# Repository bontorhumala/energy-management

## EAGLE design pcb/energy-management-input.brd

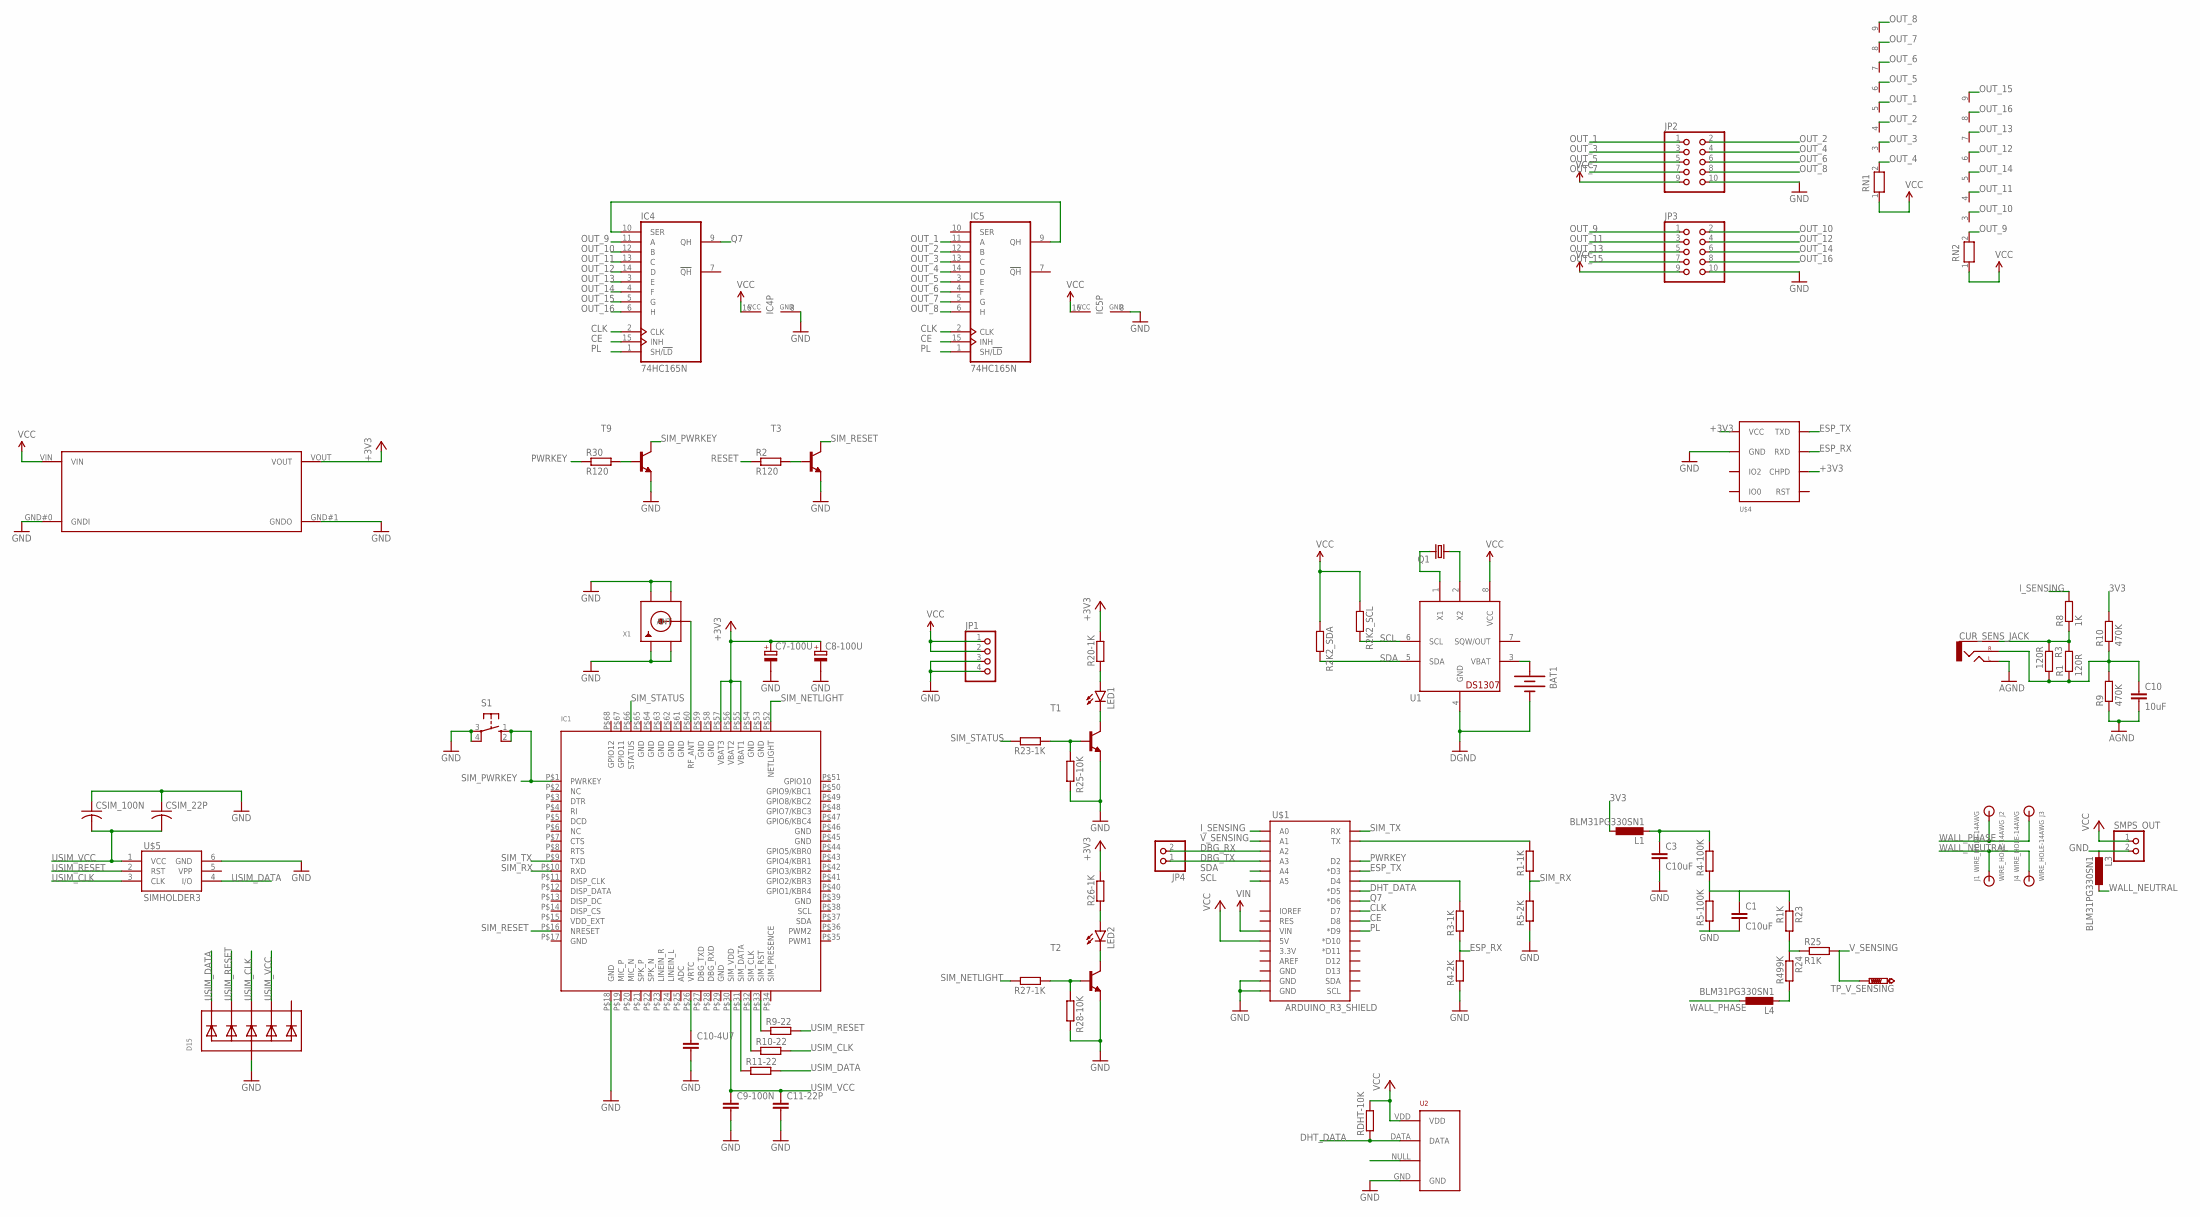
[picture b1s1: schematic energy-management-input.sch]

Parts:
BAT1: BATTERY20PTH; BATTCOM_20MM_PTH
C1, C3: C10uF; C0805
C7-100U, C8-100U: CPOL-EU153CLV-0605; 153CLV-0605
C9-100N, C10-4U7, C11-22P: C-EUC0603; C0603
C10: 10uF; C0805
CSIM_22P, CSIM_100N: C-USC0603K; C0603K
CUR_SENS_JACK: AUDIO-JACKSMD2; AUDIO-JACK-3.5MM-SMD
D15: TVSARRAY_5LANE; SOT363
IC1: GSM_SIM900_LITERAL; SIM900_SMT
IC4, IC5: 74HC165N; DIL16
J1, J2, J3, J4: WIRE_HOLE-14AWG
JP1: PINHD-1X4; 1X04
JP2, JP3: PINHD-2X5; 2X05
JP4: PINHD-1X2; 1X02
L1, L3, L4: BLM31PG330SN1; L3216C
LED1, LED2: LED-3MM-NO_SILK; LED3MM-NS
Q1: CRYSTALTC26H; TC26H
R1: 120R; 0204/7
R1-1K, R2K2_SCL, R2K2_SDA, R3-1K, R4-2K, R5-2K, R9-22, R10-22, R11-22, R20-1K, R23-1K, R25-10K, R26-1K, R27-1K, R28-10K: R-EU_R0603; R0603
R2, R30: R120; M0805
R3: 120R; R1206
R4-100K, R5-100K: R-EU_R0805; R0805
R8: 1K; R0805
R9, R10: 470K; R0805
R23, R25: R1K; R0805
R24: R499K; R0805
RDHT-10K: R-EU_R0603; R0603
RN1, RN2: RN08; RN-9
S1: 10-XX; B3F-10XX
SMPS_OUT: PINHD-1X2; 1X02
T1, T2, T3, T9: MMBT2222ALT1-NPN-SOT23-BEC; SOT23-BEC
TP_V_SENSING: PTR1PAD1-13; P1-13
U1: DS1307; DIL08
U2: RHT03_DHT-22_AM2302; RHT03_DHT-22
U$1: ARDUINO_R3_SHIELD; UNO_R3_SHIELD
U$2: DCDCMODULE
U$4: ESP8266
U$5: SIMHOLDER3
X1: SMACONNECTOR; SMA90_DIP

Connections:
3V3: L1.1, R10.2
+3V3: C7-100U.+, C8-100U.+, IC1.P$55 (VBAT1), IC1.P$56 (VBAT2), IC1.P$57 (VBAT3), R20-1K.2, R26-1K.2, U$2.VOUT, U$4.CHPD, U$4.VCC
AGND: C10.2, CUR_SENS_JACK.TIP (LEFT), R9.1
CE: IC4.15 (INH), IC5.15 (INH), U$1.D8
CLK: IC4.2 (CLK), IC5.2 (CLK), U$1.D7
DBG_RX: JP4.2, U$1.A2
DBG_TX: JP4.1, U$1.A3
DHT_DATA: RDHT-10K.1, U2.DATA, U$1.D5 (*D5)
ESP_RX: R3-1K.1, R4-2K.2, U$4.RXD
ESP_TX: U$1.D3 (*D3), U$4.TXD
GND: BAT1.2 (-), C1.2, C3.2, C7-100U.-, C8-100U.-, C9-100N.2, C10-4U7.2, C11-22P.2, CSIM_22P.1, CSIM_100N.1, D15.2 (A), IC1.P$17 (GND), IC1.P$18 (GND), IC1.P$29 (GND), IC1.P$39 (GND), IC1.P$45 (GND), IC1.P$46 (GND), IC1.P$53 (GND), IC1.P$54 (GND), IC1.P$58 (GND), IC1.P$59 (GND), IC1.P$61 (GND), IC1.P$62 (GND), IC1.P$63 (GND), IC1.P$64 (GND), IC1.P$65 (GND), IC4.8 (GND), IC5.8 (GND), JP1.3, JP1.4, JP2.10, JP3.10, L3.2, R4-2K.1, R5-2K.1, R5-100K.1, R25-10K.2, R28-10K.2, S1.3, S1.4 (P1), SMPS_OUT.2, T1.E, T2.E, T3.E, T9.E, U1.4 (GND), U2.GND, U$1.GND@0 (GND), U$1.GND@1 (GND), U$2.GND#0 (GNDI), U$2.GND#1 (GNDO), U$4.GND, U$5.6 (GND), X1.GND1, X1.GND2, X1.GND3, X1.GND4
GPIO11: IC1.P$67 (GPIO11)
GPIO12: IC1.P$68 (GPIO12)
I_SENSING: R8.2, U$1.A0
unnamed: C3.1, L1.2, R4-100K.2
unnamed: IC1.P$31 (SIM_DATA), R11-22.1
unnamed: IC1.P$32 (SIM_CLK), R10-22.1
unnamed: IC1.P$33 (SIM_RST), R9-22.1
unnamed: C10-4U7.1, IC1.P$26 (VRTC)
unnamed: IC1.P$60 (RF_ANT), X1.ANTENNA (ANT)
unnamed: R1-1K.2, U$1.TX
unnamed: LED1.A, R20-1K.1
unnamed: LED1.K (C), T1.C
unnamed: R23-1K.1, R25-10K.1, T1.B
unnamed: LED2.A, R26-1K.1
unnamed: LED2.K (C), T2.C
unnamed: R27-1K.1, R28-10K.1, T2.B
unnamed: R30.2, T9.B
unnamed: R2.2, T3.B
unnamed: Q1.1, U1.2 (X2)
unnamed: R3-1K.2, U$1.D4
unnamed: Q1.2, U1.1 (X1)
unnamed: C1.1, R4-100K.1, R5-100K.2, R23.1
unnamed: R23.2, R24.1, R25.1
unnamed: L4.2, R24.2
unnamed: BAT1.1 (+), U1.3 (VBAT)
unnamed: CUR_SENS_JACK.SLEEVE, R1.2, R3.1, R8.1
unnamed: C10.1, CUR_SENS_JACK.RING (RIGHT), R1.1, R3.2, R9.2, R10.1
unnamed: IC4.10 (SER), IC5.9 (QH)
OUT_1: IC5.11 (A), JP2.1, RN1.5
OUT_2: IC5.12 (B), JP2.2, RN1.4
OUT_3: IC5.13 (C), JP2.3, RN1.3
OUT_4: IC5.14 (D), JP2.4, RN1.2
OUT_5: IC5.3 (E), JP2.5, RN1.6
OUT_6: IC5.4 (F), JP2.6, RN1.7
OUT_7: IC5.5 (G), JP2.7, RN1.8
OUT_8: IC5.6 (H), JP2.8, RN1.9
OUT_9: IC4.11 (A), JP3.1, RN2.2
OUT_10: IC4.12 (B), JP3.2, RN2.3
OUT_11: IC4.13 (C), JP3.3, RN2.4
OUT_12: IC4.14 (D), JP3.4, RN2.6
OUT_13: IC4.3 (E), JP3.5, RN2.7
OUT_14: IC4.4 (F), JP3.6, RN2.5
OUT_15: IC4.5 (G), JP3.7, RN2.9
OUT_16: IC4.6 (H), JP3.8, RN2.8
PL: IC4.1 (SH/!LD), IC5.1 (SH/!LD), U$1.D9 (*D9)
PWRKEY: R30.1, U$1.D2
Q7: IC4.9 (QH), U$1.D6 (*D6)
RESET: R2.1
SCL: R2K2_SCL.2, U1.6 (SCL), U$1.A5
SDA: R2K2_SDA.2, U1.5 (SDA), U$1.A4
SIM_NETLIGHT: IC1.P$52 (NETLIGHT), R27-1K.2
SIM_PWRKEY: IC1.P$1 (PWRKEY), S1.1 (S), S1.2 (S1), T9.C
SIM_RESET: IC1.P$16 (NRESET), T3.C
SIM_RX: IC1.P$10 (RXD), R1-1K.1, R5-2K.2
SIM_STATUS: IC1.P$66 (STATUS), R23-1K.2
SIM_TX: IC1.P$9 (TXD), U$1.RX
USIM_CLK: D15.4 (C3), R10-22.2, U$5.3 (CLK)
USIM_DATA: D15.1 (C1), R11-22.2, U$5.4 (I/O)
USIM_RESET: D15.3 (C2), R9-22.2, U$5.2 (RST)
USIM_VCC: C9-100N.1, C11-22P.1, CSIM_22P.2, CSIM_100N.2, D15.5 (C4), IC1.P$30 (SIM_VDD), U$5.1 (VCC)
VCC: IC4.16 (VCC), IC5.16 (VCC), JP1.1, JP1.2, JP2.9, JP3.9, R2K2_SCL.1, R2K2_SDA.1, RDHT-10K.2, RN1.1, RN2.1, SMPS_OUT.1, U1.8 (VCC), U2.VDD, U$1.5V, U$2.VIN
VIN: U$1.VIN
V_SENSING: R25.2, TP_V_SENSING.TP, U$1.A1
WALL_NEUTRAL: J1.P$1, J4.P$1, L3.1
WALL_PHASE: J2.P$1, J3.P$1, L4.1

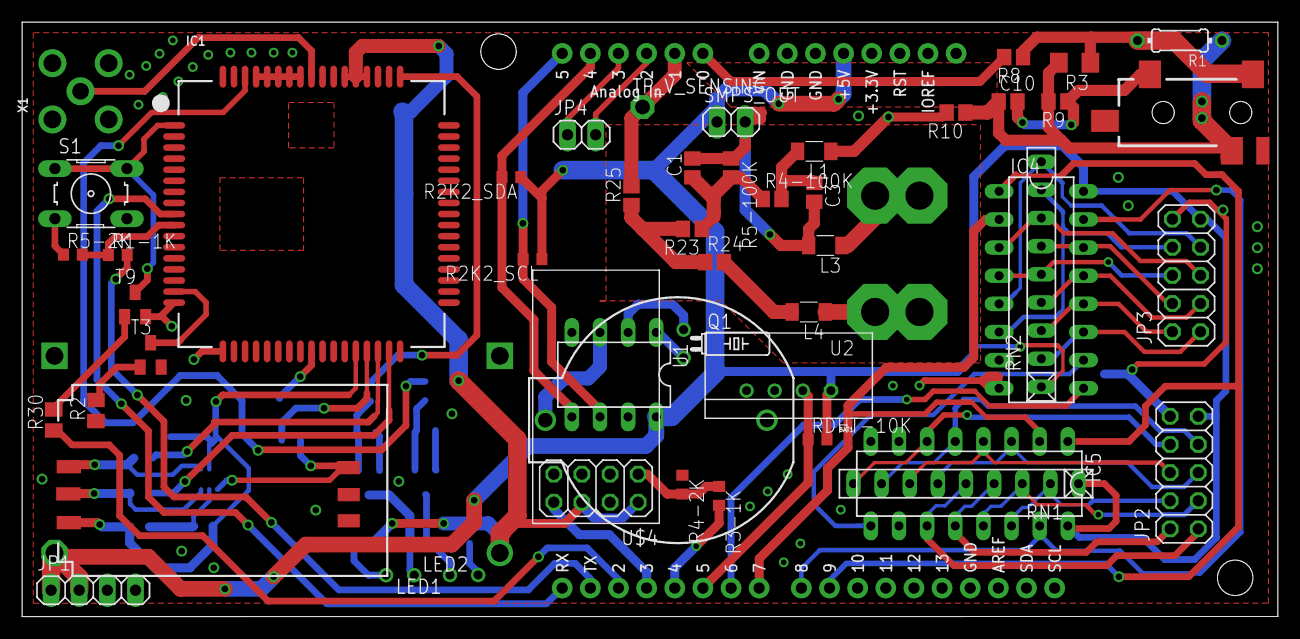
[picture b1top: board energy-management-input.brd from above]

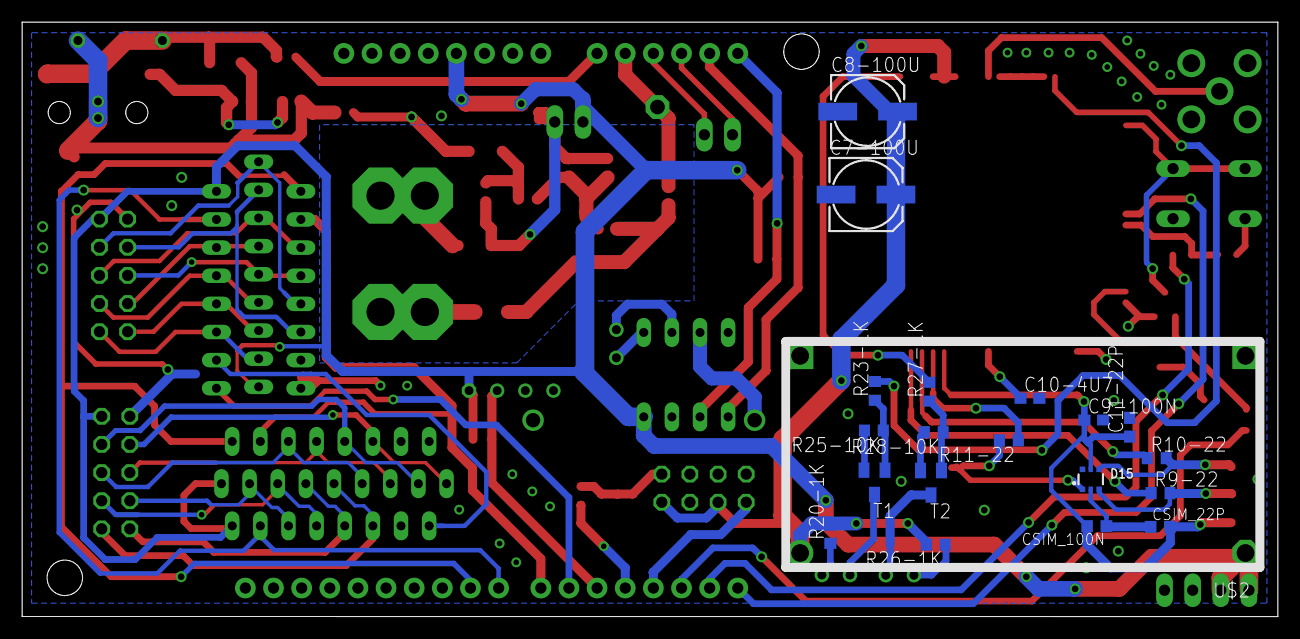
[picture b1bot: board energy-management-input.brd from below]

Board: 2 copper layers, 113.3 x 53.7 mm, 74 parts (20 on the bottom side), 72 nets.

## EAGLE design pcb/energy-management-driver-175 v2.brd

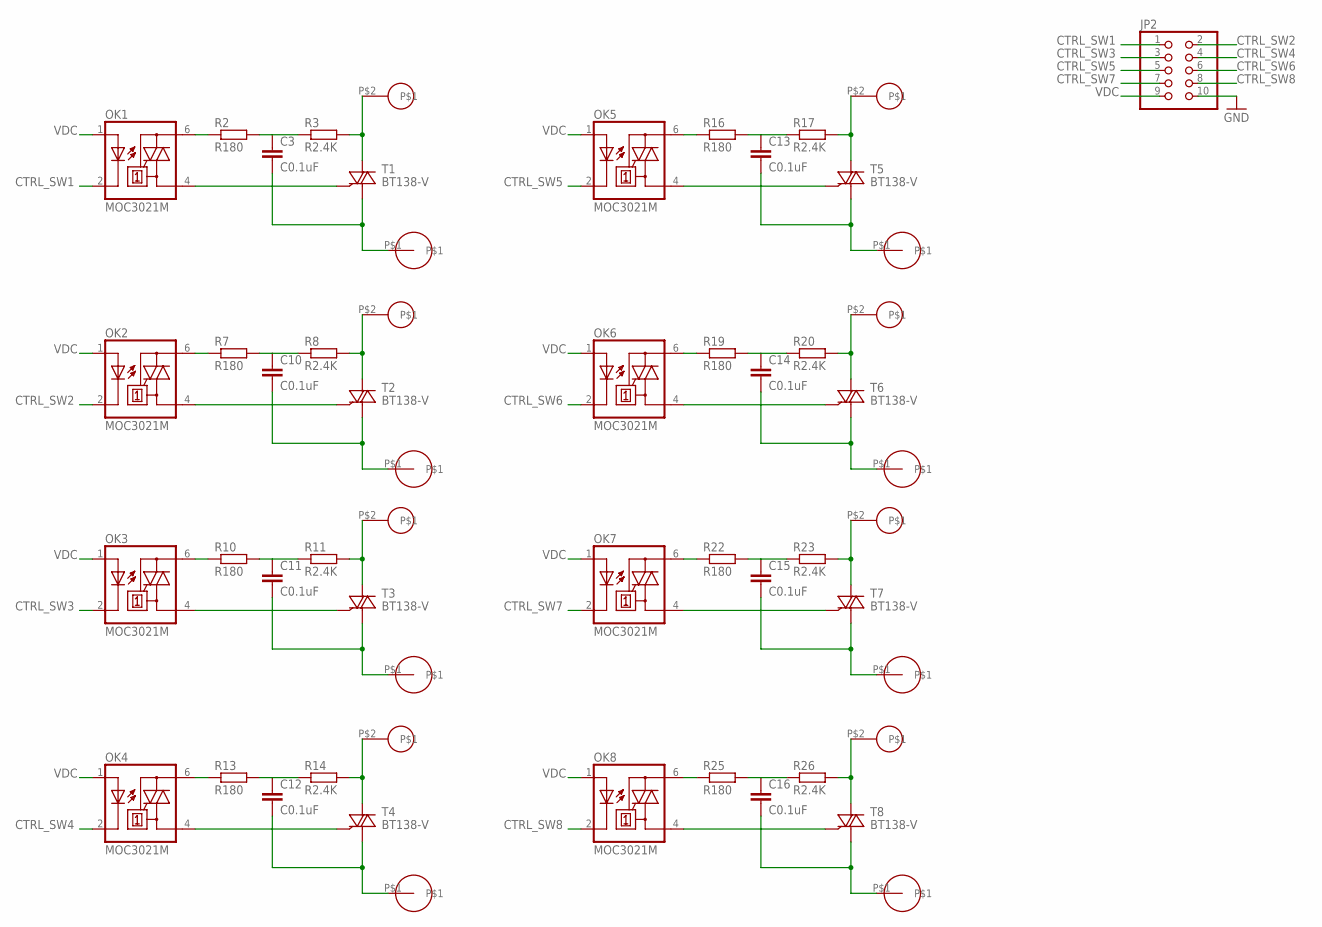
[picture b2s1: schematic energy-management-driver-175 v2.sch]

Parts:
C3, C10, C11, C12, C13, C14, C15, C16: C0.1uF; C0805
JP2: PINHD-2X5; 2X05
OK1, OK2, OK3, OK4, OK5, OK6, OK7, OK8: MOC3021M; DIL06
R2, R7, R10, R13, R16, R19, R22, R25: R180; M0805
R3, R8, R11, R14, R17, R20, R23, R26: R2.4K; M0805
T1, T2, T3, T4, T5, T6, T7, T8: BT138-V; TO220BV
U$1, U$2, U$3, U$4, U$5, U$6, U$7, U$8: CONN-SKUN
U$9, U$10, U$11, U$12, U$13, U$14, U$15, U$16: CONN-CABLE

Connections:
CTRL_SW1: JP2.1, OK1.2 (C)
CTRL_SW2: JP2.2, OK2.2 (C)
CTRL_SW3: JP2.3, OK3.2 (C)
CTRL_SW4: JP2.4, OK4.2 (C)
CTRL_SW5: JP2.5, OK5.2 (C)
CTRL_SW6: JP2.6, OK6.2 (C)
CTRL_SW7: JP2.7, OK7.2 (C)
CTRL_SW8: JP2.8, OK8.2 (C)
GND: JP2.10
unnamed: OK1.6 (A2), R2.1
unnamed: C3.1, R2.2, R3.1
unnamed: OK1.4 (A1), T1.G
unnamed: C3.2, T1.T1 (A1), U$9.P$1
unnamed: R3.2, T1.T2 (A2), U$1.P$2
unnamed: OK2.6 (A2), R7.1
unnamed: C10.1, R7.2, R8.1
unnamed: OK2.4 (A1), T2.G
unnamed: C10.2, T2.T1 (A1), U$11.P$1
unnamed: OK3.6 (A2), R10.1
unnamed: C11.1, R10.2, R11.1
unnamed: OK3.4 (A1), T3.G
unnamed: C11.2, T3.T1 (A1), U$14.P$1
unnamed: OK4.6 (A2), R13.1
unnamed: C12.1, R13.2, R14.1
unnamed: OK4.4 (A1), T4.G
unnamed: C12.2, T4.T1 (A1), U$13.P$1
unnamed: OK5.6 (A2), R16.1
unnamed: C13.1, R16.2, R17.1
unnamed: OK5.4 (A1), T5.G
unnamed: C13.2, T5.T1 (A1), U$10.P$1
unnamed: OK6.6 (A2), R19.1
unnamed: C14.1, R19.2, R20.1
unnamed: OK6.4 (A1), T6.G
unnamed: C14.2, T6.T1 (A1), U$12.P$1
unnamed: OK7.6 (A2), R22.1
unnamed: C15.1, R22.2, R23.1
unnamed: OK7.4 (A1), T7.G
unnamed: C15.2, T7.T1 (A1), U$15.P$1
unnamed: OK8.6 (A2), R25.1
unnamed: C16.1, R25.2, R26.1
unnamed: OK8.4 (A1), T8.G
unnamed: C16.2, T8.T1 (A1), U$16.P$1
unnamed: R8.2, T2.T2 (A2), U$2.P$2
unnamed: R11.2, T3.T2 (A2), U$3.P$2
unnamed: R14.2, T4.T2 (A2), U$4.P$2
unnamed: R26.2, T8.T2 (A2), U$5.P$2
unnamed: R23.2, T7.T2 (A2), U$6.P$2
unnamed: R20.2, T6.T2 (A2), U$7.P$2
unnamed: R17.2, T5.T2 (A2), U$8.P$2
VDC: JP2.9, OK1.1 (A), OK2.1 (A), OK3.1 (A), OK4.1 (A), OK5.1 (A), OK6.1 (A), OK7.1 (A), OK8.1 (A)

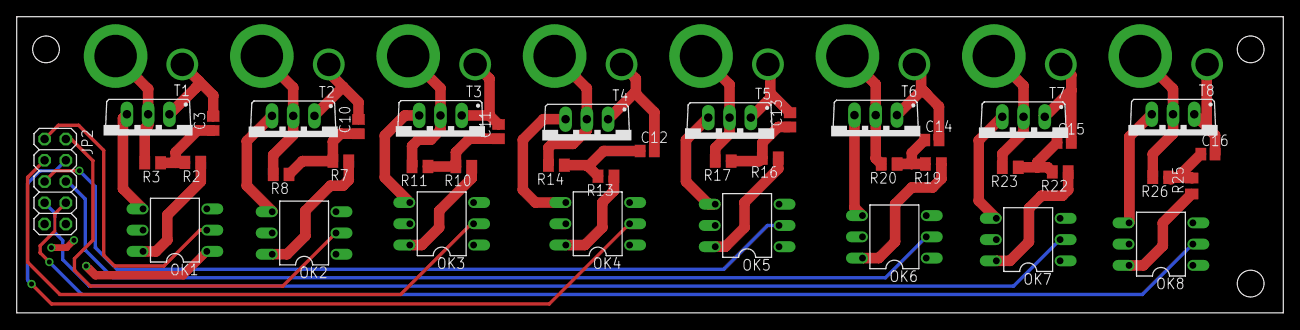
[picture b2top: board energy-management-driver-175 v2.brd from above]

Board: 2 copper layers, 151.4 x 35.4 mm, 57 parts (0 on the bottom side), 49 nets.

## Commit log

2014-12-03 :confetti_ball: Added .gitattributes & .gitignore files
2014-12-03 initial addition: pcb and sketch
2014-12-03 added voltage and current measurement circuit
2014-12-03 routing shift register
2014-12-04 pcb with shift register and dht22
2014-12-04 put batt and reg on bottom, dht, ds, wifi on top
2014-12-04 remove resistor and cutout on analog line
2014-12-04 add hole
2014-12-04 move via
2014-12-04 remove unnecessary sensing 2 circuit
2014-12-04 change route
2014-12-04 revise UI
2014-12-05 mobile app will not have scheduling
2014-12-05 using tabbed UI
2014-12-05 change UI to mobile
2014-12-05 UI mobile finished, need integration to cloud and device
2014-12-05 adding new settings form
2014-12-05 started integration to server
2014-12-09 functional control working
2014-12-09 adding geofencing and geolocation background
2014-12-09 .gitignore is now working
2014-12-12 add geofencing
2014-12-12 geofence style ok
2014-12-12 geofence ok
2014-12-12 update board
2014-12-13 connect vcc to out
2014-12-14 sync graphs and overview value
2014-12-14 use resolve to smoothen experience
2014-12-15 run in android
2014-12-21 final mobile UI
2014-12-21 added casing design
    casing for protoype
2014-12-21 added firmware
2014-12-21 firmware v1
    need to test power measurement - buy sim card
2014-12-21 add shiftout
    shiftout needed by output to control electrical lines
2014-12-21 update board
    SH_CP and DS cannot be place on Eth pin
2014-12-22 add driver board
2015-01-05 updated driver board and add input board
    Update driver 175 board to use skun terminal. Also add input board for
    hotel asia
2015-01-05 Finished Input Board
    Input board schematic and routing finished
2015-01-06 application use Crosswork
2015-01-07 mobile app geofencing ok on dummy geolocation, release app not detecting
2015-01-07 mobile app geofencing relies on wifi and cell, notification needs modification
2015-01-08 adding socket still not working
2015-01-09 socket ok on ubuntu server but not on esp
2015-01-09 firmware initial working
2015-01-09 Calibrate Emon
    Calibrate voltage and phase shift
2015-01-09 Calibration Emon 2
    Calibration phase shift still not ok
2015-01-09 seems like esp network problem - need to allow app to start w/o inet connection
2015-01-09 work - can send config from emos to plug
2015-01-12 sync OK
2015-01-13 Adding shift register to controller
2015-01-13 can get talkback, need parse response
2015-01-13 able to parse && ##, need to control driver
2015-01-13 need convert char array to driver command
2015-01-14 panel finished, need to modify pcb holes and make casing
2015-01-15 update holes in driver board
2015-01-16 added hotel asia code
2015-01-19 application send && and ## command
2015-01-19 can connect to devices, need to verify power and temperatures data
2015-01-19 application ok, need testing with panel device
2015-02-05 update boards and firmware works for energy-management v2
2015-02-05 need to fix graphs to be readable
2015-02-05 need to fix graphs

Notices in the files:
parts and their libraries:
SparkFun-Aesthetics: Licensing: Creative Commons ShareAlike 4.0 International - https://creativecommons.org/licenses/by-sa/4.0
SparkFun: Licensing: CC v3.0 Share-Alike You are welcome to use this library for commercial purposes.
